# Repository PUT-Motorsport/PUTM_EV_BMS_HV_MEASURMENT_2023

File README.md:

# PUTM_EV_BMSHV_MEASURMENT_2023
BMS HV measurment boards (A &amp; B) for PM07/8 vehicle.
Replaced soldered IDC tape brigde with 02x03 IDC connnectors.

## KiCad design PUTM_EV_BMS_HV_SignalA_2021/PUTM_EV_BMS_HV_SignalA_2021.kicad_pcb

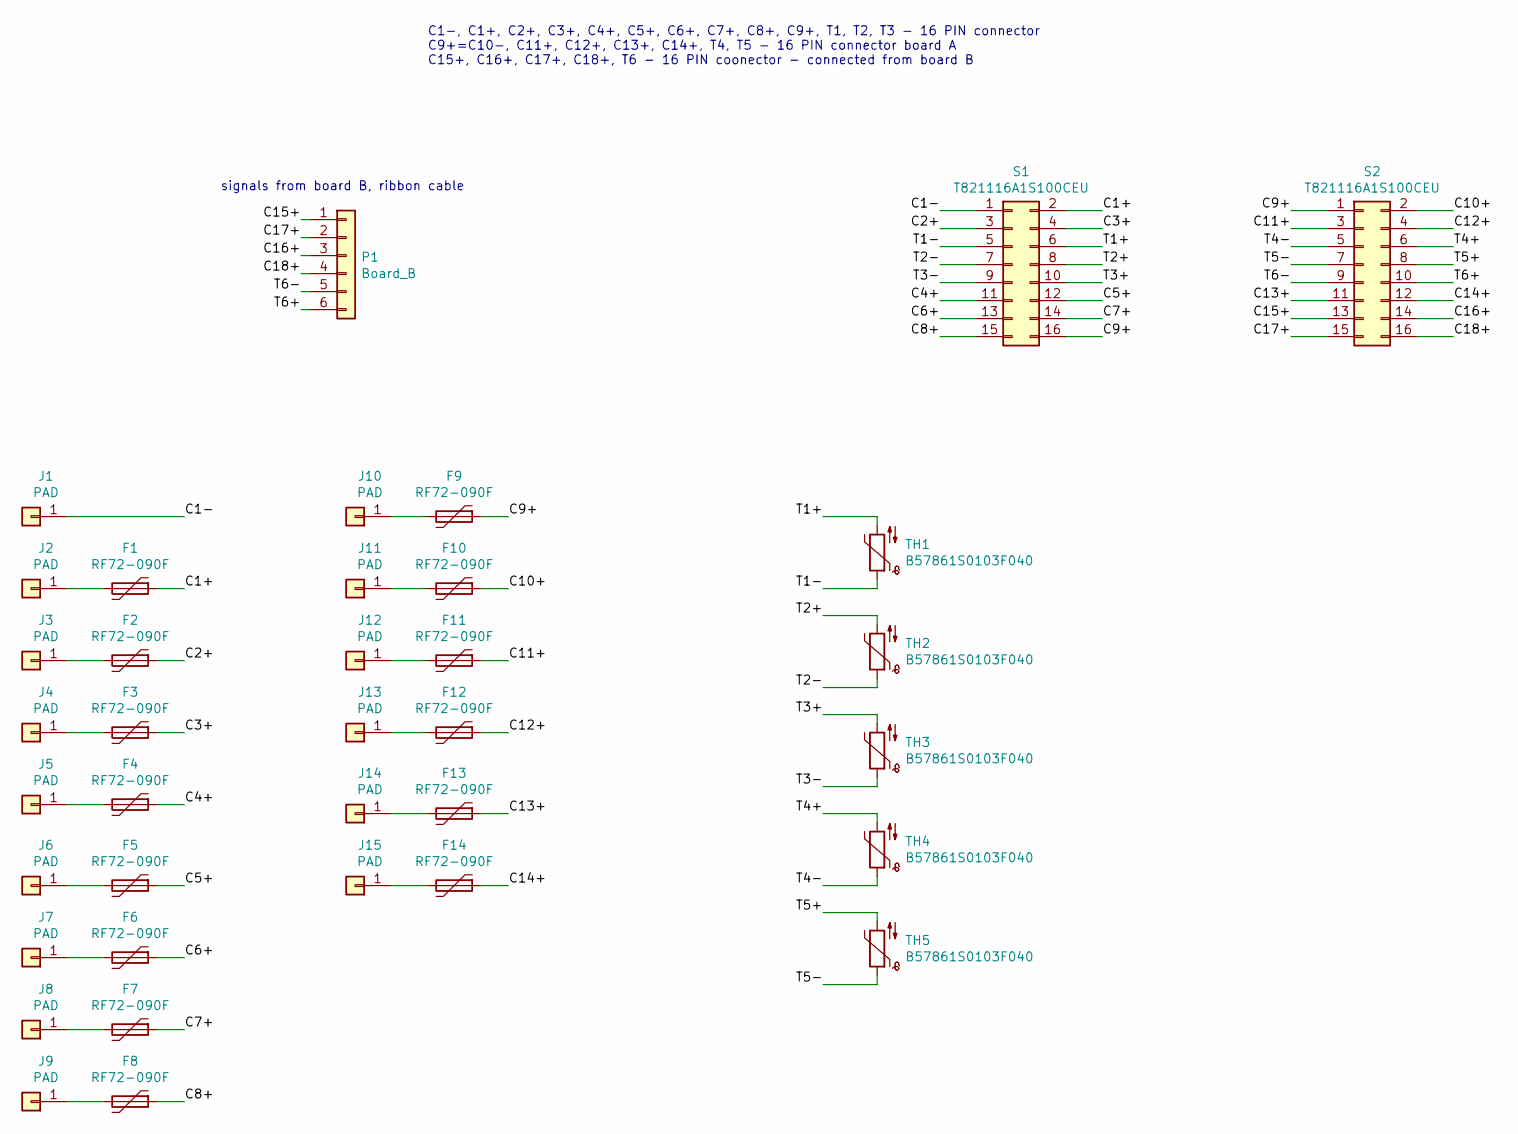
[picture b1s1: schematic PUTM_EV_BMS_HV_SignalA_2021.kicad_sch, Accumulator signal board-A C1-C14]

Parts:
F1, F2, F3, F4, F5, F6, F7, F8, F9, F10, F11, F12, F13, F14: RF72-090F; Fuse_Bourns_MF-RG400
J1, J2, J3, J4, J5, J6, J7, J8, J9, J10, J11, J12, J13, J14, J15: PAD; CELL_PAD
P1: Board_B; IDC-Header_2x03_P2.54mm_Vertical
S1, S2: T821116A1S100CEU; IDC-Header_2x08_P2.54mm_Vertical
TH1, TH2, TH3, TH4, TH5: B57861S0103F040; PinHeader_1x02_P1.27mm_Vertical

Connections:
/C1+: F1.1, S1.2
/C1-: J1.1, S1.1
/C2+: F2.1, S1.3
/C3+: F3.1, S1.4
/C4+: F4.1, S1.11
/C5+: F5.1, S1.12
/C6+: F6.1, S1.13
/C7+: F7.1, S1.14
/C8+: F8.1, S1.15
/C9+: F9.1, S1.16, S2.1
/C10+: F10.1, S2.2
/C11+: F11.1, S2.3
/C12+: F12.1, S2.4
/C13+: F13.1, S2.11
/C14+: F14.1, S2.12
/C15+: P1.1, S2.13
/C16+: P1.3, S2.14
/C17+: P1.2, S2.15
/C18+: P1.4, S2.16
/T1+: S1.6, TH1.2
/T1-: S1.5, TH1.1
/T2+: S1.8, TH2.2
/T2-: S1.7, TH2.1
/T3+: S1.10, TH3.2
/T3-: S1.9, TH3.1
/T4+: S2.6, TH4.2
/T4-: S2.5, TH4.1
/T5+: S2.8, TH5.2
/T5-: S2.7, TH5.1
/T6+: P1.6, S2.10
/T6-: P1.5, S2.9
unnamed: F1.2, J2.1
unnamed: F2.2, J3.1
unnamed: F3.2, J4.1
unnamed: F4.2, J5.1
unnamed: F5.2, J6.1
unnamed: F6.2, J7.1
unnamed: F7.2, J8.1
unnamed: F8.2, J9.1
unnamed: F9.2, J10.1
unnamed: F10.2, J11.1
unnamed: F11.2, J12.1
unnamed: F12.2, J13.1
unnamed: F13.2, J14.1
unnamed: F14.2, J15.1

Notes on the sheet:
signals from board B, ribbon cable
C1-, C1+, C2+, C3+, C4+, C5+, C6+, C7+, C8+, C9+, T1, T2, T3 - 16 PIN connector C9+=C10-, C11+, C12+, C13+, C14+, T4, T5 - 16 PIN connector board A C15+, C16+, C17+, C18+, T6 - 16 PIN coonector - connected from board B

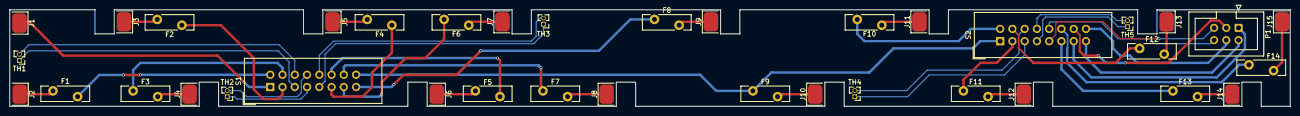
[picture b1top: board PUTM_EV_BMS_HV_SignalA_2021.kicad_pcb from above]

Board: 2 copper layers, 265.2 x 20.0 mm, 37 parts (0 on the bottom side), 45 nets.

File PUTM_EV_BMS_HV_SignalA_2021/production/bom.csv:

Designator,Footprint,Quantity,Value,LCSC Part #
"F1, F10, F11, F12, F13, F14, F2, F3, F4, F5, F6, F7, F8, F9",Fuse_Bourns_MF-RG400,14,RF72-090F,
"J1, J10, J11, J12, J13, J14, J15, J2, J3, J4, J5, J6, J7, J8, J9",CELL_PAD,15,PAD,
P1,IDC-Header_2x03_P2.54mm_Vertical,1,Board_B,
"S1, S2",IDC-Header_2x08_P2.54mm_Vertical,2,T821116A1S100CEU,
"TH1, TH2, TH3, TH4, TH5",PinHeader_1x02_P1.27mm_Vertical,5,B57861S0103F040,

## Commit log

2023-07-25 initial commit - upgraded 2021 version
2023-07-25 removed gitignored files
